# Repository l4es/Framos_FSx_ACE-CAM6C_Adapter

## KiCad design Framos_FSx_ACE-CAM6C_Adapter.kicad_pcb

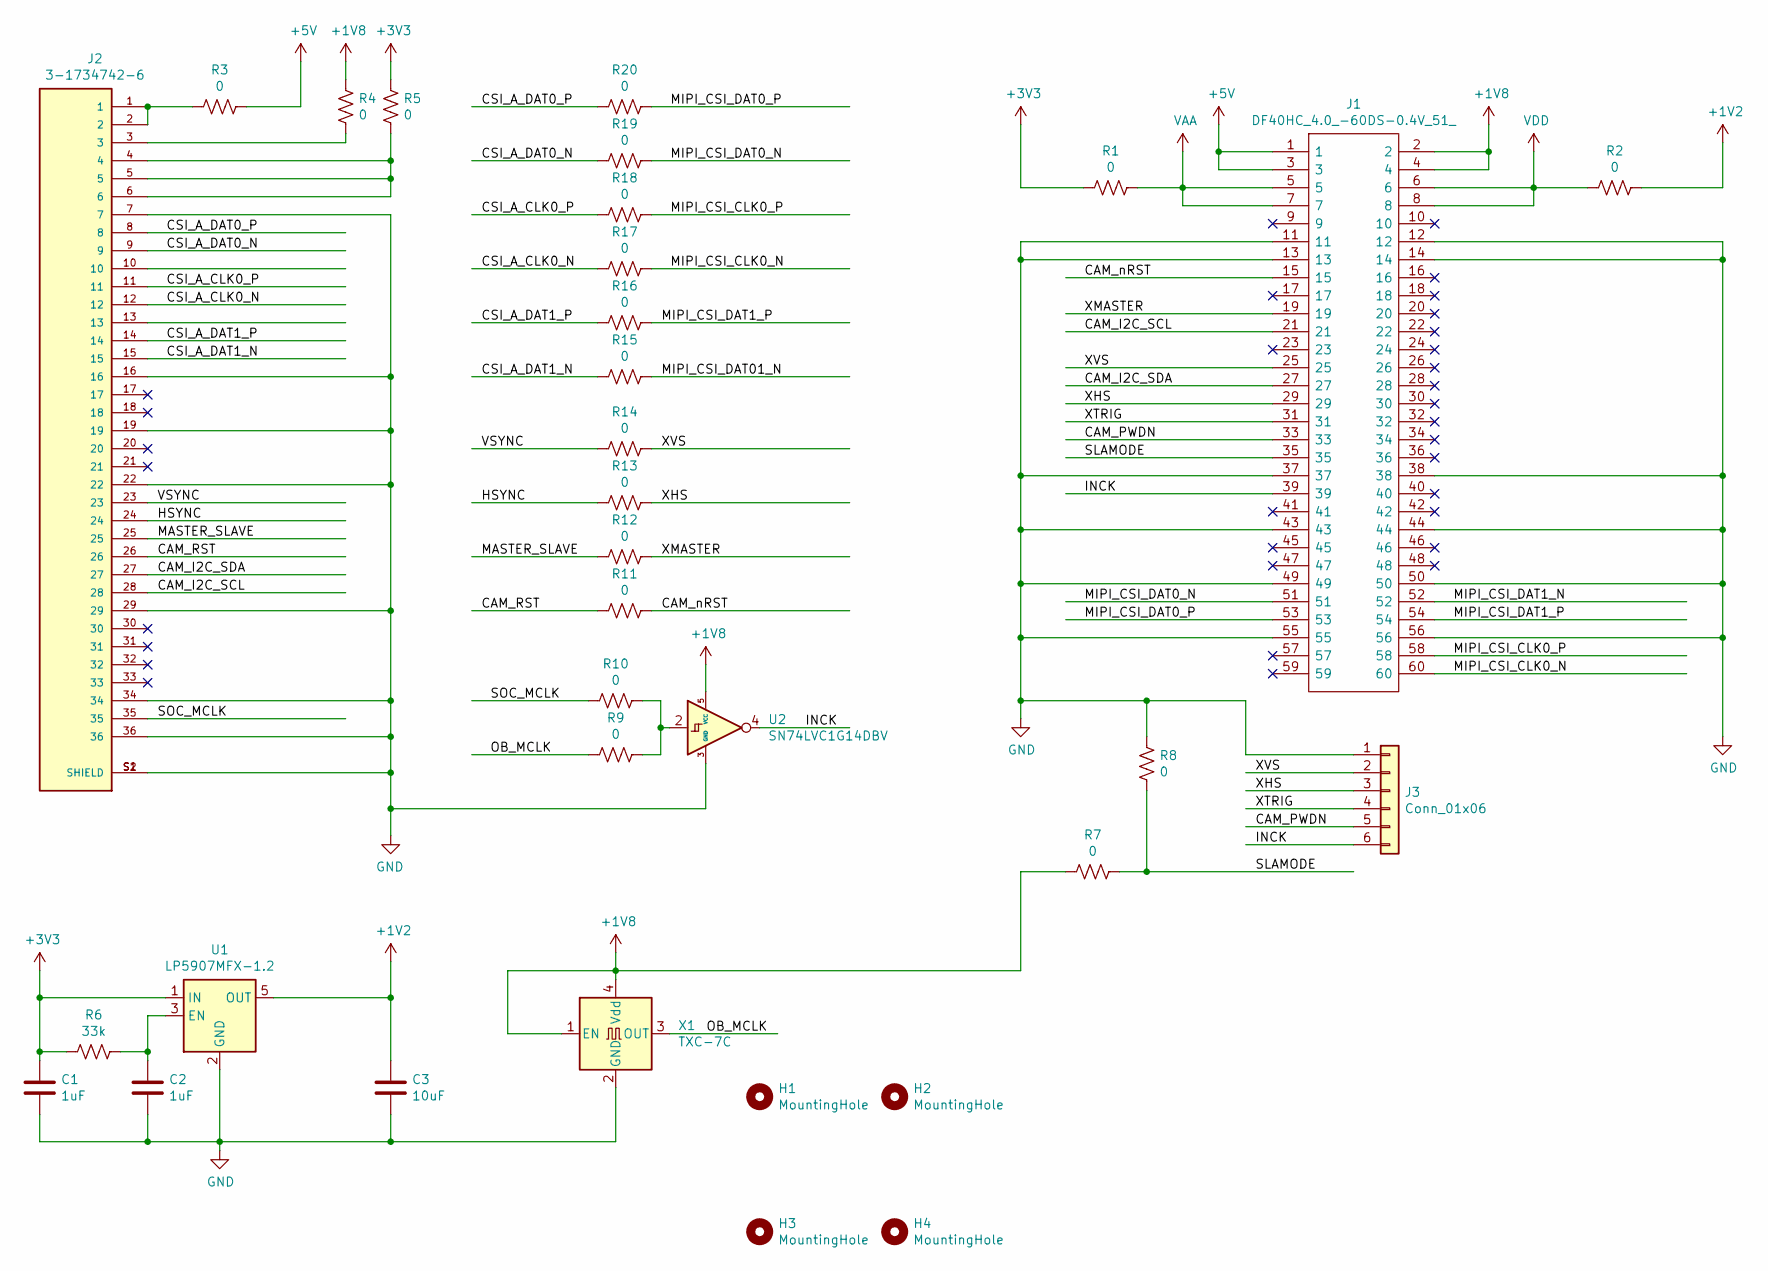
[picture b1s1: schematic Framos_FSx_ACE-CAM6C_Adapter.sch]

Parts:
C1, C2: 1uF; C_0603_1608Metric_Pad1.08x0.95mm_HandSolder
C3: 10uF; C_0603_1608Metric_Pad1.08x0.95mm_HandSolder
H1, H2, H3, H4: MountingHole; MountingHole_2.2mm_M2
J1: DF40HC_4.0_-60DS-0.4V_51_; DF40HC4060DS04V51; Manufacturer_Part_Number DF40HC(4.0)-60DS-0.4V(51); Mouser Part Number 798-DF4HC4060DS04V51
J2: 3-1734742-6; TE_3-1734742-6; PARTREV P
J3: Conn_01x06; PinHeader_1x06_P2.54mm_Vertical
R1, R2, R3, R4, R5, R7, R8, R9, R10, R11, R12, R13, R14, R15, R16, R17, R18, R19, R20: 0; R_0805_2012Metric_Pad1.20x1.40mm_HandSolder
R6: 33k; R_0805_2012Metric_Pad1.20x1.40mm_HandSolder
U1: LP5907MFX-1.2; SOT-23-5
U2: SN74LVC1G14DBV; SOT-23-5
X1: TXC-7C; Oscillator_SMD_TXC_7C-4Pin_5.0x3.2mm

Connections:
+1V2: C3.1, R2.1, U1.5 (OUT)
+1V8: J1.2, J1.4, R4.1, R7.2, U2.5 (VCC), X1.1 (EN), X1.4 (Vdd)
+3V3: C1.1, R1.2, R5.1, R6.2, U1.1 (IN)
+5V: J1.1, J1.3, R3.1
/CAM_I2C_SCL: J1.21, J2.28
/CAM_I2C_SDA: J1.27, J2.27
/CAM_PWDN: J1.33, J3.5
/CAM_RST: J2.26, R11.2
/CAM_nRST: J1.15, R11.1
/CSI_A_CLK0_N: J2.12, R17.2
/CSI_A_CLK0_P: J2.11, R18.2
/CSI_A_DAT0_N: J2.9, R19.2
/CSI_A_DAT0_P: J2.8, R20.2
/CSI_A_DAT1_N: J2.15, R15.2
/CSI_A_DAT1_P: J2.14, R16.2
/HSYNC: J2.24, R13.2
/INCK: J1.39, J3.6, U2.4
/MASTER_SLAVE: J2.25, R12.2
/MIPI_CSI_CLK0_N: J1.60, R17.1
/MIPI_CSI_CLK0_P: J1.58, R18.1
/MIPI_CSI_DAT0_N: J1.51, R19.1
/MIPI_CSI_DAT0_P: J1.53, R20.1
/MIPI_CSI_DAT01_N: R15.1
/MIPI_CSI_DAT1_N: J1.52
/MIPI_CSI_DAT1_P: J1.54, R16.1
/OB_MCLK: R9.2, X1.3 (OUT)
/SLAMODE: J1.35, R7.1, R8.2
/SOC_MCLK: J2.35, R10.2
/VSYNC: J2.23, R14.2
/XHS: J1.29, J3.3, R13.1
/XMASTER: J1.19, R12.1
/XTRIG: J1.31, J3.4
/XVS: J1.25, J3.2, R14.1
GND: C1.2, C2.2, C3.2, J1.11, J1.12, J1.13, J1.14, J1.37, J1.38, J1.43, J1.44, J1.49, J1.50, J1.55, J1.56, J2.7, J2.16, J2.19, J2.22, J2.29, J2.34, J2.36, J2.S1 (SHIELD), J2.S2 (SHIELD), J3.1, R8.1, U1.2 (GND), U2.3 (GND), X1.2 (GND)
unnamed: C2.1, R6.1, U1.3 (EN)
unnamed: J2.1, J2.2, R3.2
unnamed: J2.3, R4.2
unnamed: J2.4, J2.5, J2.6, R5.2
unnamed: R9.1, R10.1, U2.2
VAA: J1.5, J1.7, R1.1
VDD: J1.6, J1.8, R2.2

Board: 2 copper layers, 33 parts (0 on the bottom side), 39 nets, no tracks yet.

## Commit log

2021-05-24 Add schematic drawing
2021-05-24 Change component and associated libraries
2021-05-24 Change schemtic component
2021-05-25 Assign footprints and genrate netlist
